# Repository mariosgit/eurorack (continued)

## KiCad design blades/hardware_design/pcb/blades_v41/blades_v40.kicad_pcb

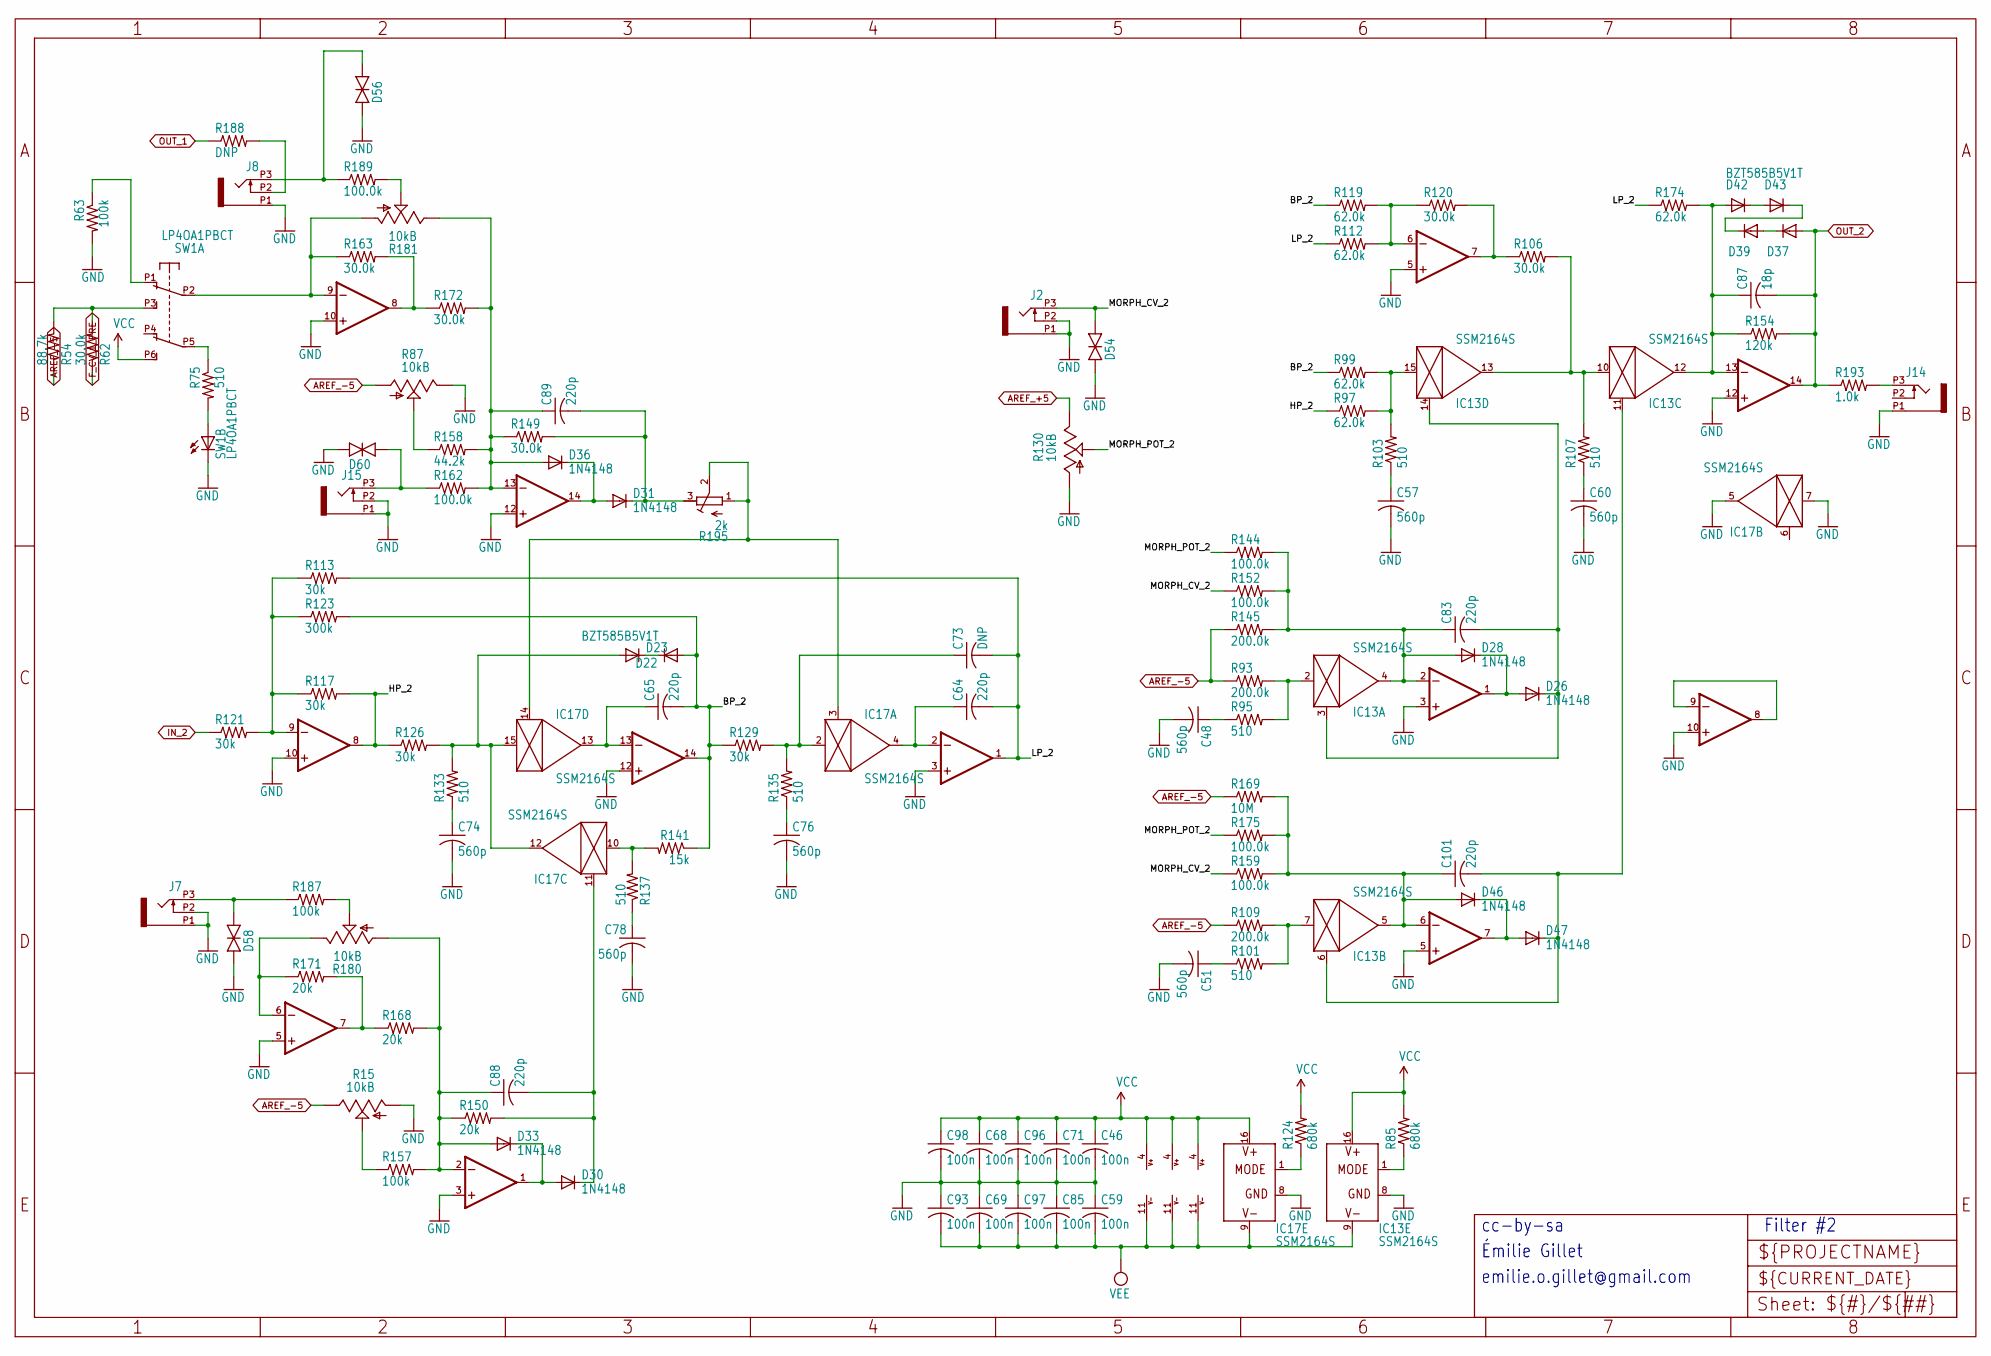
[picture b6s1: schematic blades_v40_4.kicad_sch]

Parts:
C46, C59, C68, C69, C71, C85, C93, C96, C97, C98: 100n; C0402
C48, C51, C57, C60, C74, C76, C78: 560p; C0402
C64, C65, C83, C88, C89, C101: 220p; C0402
C73: DNP; C0402
C87: 18p; C0402
D22, D23, D37, D39, D42, D43: BZT585B5V1T; SOD523
D26, D28, D30, D31, D33, D36, D46, D47: 1N4148; SOD523
D54, D56, D58, D60: TVS; 0603
IC13, IC17: SSM2164S; SOIC16N
IC15, IC21: OPA1679PW; TSSOP14_065
IC20: TL074PW; TSSOP14_065
J2, J7, J8, J14, J15: PJ301_THONKICONNTME; WQP_PJ_301M_TME
R15, R87, R130: 10kB; ALPS_POT_VERTICAL_PS
R54: 88.7k; R0402
R62, R106, R120, R149, R163, R172: 30.0k; R0402
R63, R157, R187: 100k; R0402
R75, R95, R101, R103, R107, R133, R135, R137: 510; R0402
R85, R124: 680k; R0402
R93, R109, R145: 200.0k; R0402
R97, R99, R112, R119, R174: 62.0k; R0402
R113, R117, R121, R126, R129: 30k; R0402
R123: 300k; R0402
R141: 15k; R0402
R144, R152, R159, R162, R175, R189: 100.0k; R0402
R150, R168, R171: 20k; R0402
R154: 120k; R0402
R158: 44.2k; R0402
R169: 10M; R0402
R180, R181: 10kB; ALPS_POT_NARROW
R188: DNP; R0603
R193: 1.0k; R0603
R195: 2k; RTRIM3296W
SW1: LP4OA1PBCT

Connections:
/blades_v40_4/BP_2: C65.2, D22.A, IC15.14 (OUT), R99.1, R119.1, R123.2, R129.1, R141.1
/blades_v40_4/HP_2: IC15.8 (OUT), R97.1, R117.2, R126.1
/blades_v40_4/LP_2: C64.2, C73.2, IC15.1 (OUT), R112.1, R113.2, R174.1
/blades_v40_4/MORPH_CV_2: D54.2 (C), J2.P3 (3), R152.1, R159.1
/blades_v40_4/MORPH_POT_2: R130.P$2 (S), R144.1, R175.1
AREF_+5: R130.P$1 (E); also elsewhere on the board
AREF_-5: R15.P$1 (E), R54.1, R87.P$3 (A), R93.1, R109.1, R145.1, R169.1; also elsewhere on the board
F_CV_1_PRE: R62.1; also elsewhere on the board
GND: C46.2, C48.2, C51.2, C57.2, C59.1, C60.2, C68.2, C69.1, C71.2, C74.2, C76.2, C78.2, C85.1, C93.1, C96.2, C97.1, C98.2, D54.1 (A), D56.1 (A), D58.1 (A), D60.1 (A), IC13.8 (GND), IC15.3 (+IN), IC15.5 (+IN), IC15.10 (+IN), IC15.12 (+IN), IC17.5 (OUT), IC17.7 (IN), IC17.8 (GND), IC20.3 (+IN), IC20.5 (+IN), IC20.10 (+IN), IC20.12 (+IN), IC21.3 (+IN), IC21.5 (+IN), IC21.10 (+IN), IC21.12 (+IN), J2.P1 (1), J2.P2 (2), J7.P1 (1), J7.P2 (2), J8.P1 (1), J14.P1 (1), J15.P1 (1), J15.P2 (2), R15.P$3 (A), R63.2, R87.P$1 (E), R130.P$3 (A), SW1.L2; also elsewhere on the board
IN_2: R121.1; also elsewhere on the board
unnamed: C48.1, R95.1
unnamed: C51.1, R101.1
unnamed: C57.1, R103.1
unnamed: C60.1, R107.1
unnamed: C74.1, R133.1
unnamed: C76.1, R135.1
unnamed: C78.1, R137.1
unnamed: D22.C, D23.C
unnamed: D37.C, D39.A
unnamed: D39.C, D43.C
unnamed: D42.C, D43.A
unnamed: D56.2 (C), J8.P3 (3), R189.1
unnamed: D58.2 (C), J7.P3 (3), R187.1
unnamed: D60.2 (C), J15.P3 (3), R162.1
unnamed: C83.2, D26.C, IC13.3 (CTRL), IC13.14 (CTRL)
unnamed: IC13.2 (IN), R93.2, R95.2
unnamed: C83.1, D28.A, IC13.4 (OUT), IC21.2 (-IN), R144.2, R145.2, R152.2
unnamed: C101.2, D47.C, IC13.6 (CTRL), IC13.11 (CTRL)
unnamed: IC13.7 (IN), R101.2, R109.2
unnamed: C101.1, D46.A, IC13.5 (OUT), IC21.6 (-IN), R159.2, R169.2, R175.2
unnamed: IC13.10 (IN), IC13.13 (OUT), R106.2, R107.2
unnamed: C87.1, D42.A, IC13.12 (OUT), IC21.13 (-IN), R154.1, R174.2
unnamed: IC13.15 (IN), R97.2, R99.2, R103.2
unnamed: IC13.1 (MODE), R85.1
unnamed: C64.1, IC15.2 (-IN), IC17.4 (OUT)
unnamed: IC15.6 (-IN), R112.2, R119.2, R120.1
unnamed: IC15.7 (OUT), R106.1, R120.2
unnamed: IC15.9 (-IN), R113.1, R117.1, R121.2, R123.1
unnamed: C65.1, IC15.13 (-IN), IC17.13 (OUT)
unnamed: IC17.3 (CTRL), IC17.14 (CTRL), R195.1 (E), R195.2 (S)
unnamed: C73.1, IC17.2 (IN), R129.2, R135.2
unnamed: C88.2, D30.C, IC17.11 (CTRL), R150.2
unnamed: IC17.10 (IN), R137.2, R141.2
unnamed: D23.A, IC17.12 (OUT), IC17.15 (IN), R126.2, R133.2
unnamed: IC17.1 (MODE), R124.1
unnamed: C88.1, D33.A, IC20.2 (-IN), R150.1, R157.2, R168.2, R180.P$3 (A)
unnamed: D30.A, D33.C, IC20.1 (OUT)
unnamed: IC20.6 (-IN), R171.1, R180.P$1 (E)
unnamed: IC20.7 (OUT), R168.1, R171.2
unnamed: IC20.9 (-IN), R163.1, R181.P$3 (A), SW1.P2 (A2)
unnamed: IC20.8 (OUT), R163.2, R172.1
unnamed: C89.1, D36.A, IC20.13 (-IN), R149.1, R158.2, R162.2, R172.2, R181.P$1 (E)
unnamed: D31.A, D36.C, IC20.14 (OUT)
unnamed: D26.A, D28.C, IC21.1 (OUT)
unnamed: D46.C, D47.A, IC21.7 (OUT)
unnamed: IC21.8 (OUT), IC21.9 (-IN)
unnamed: J8.P2 (2), R188.2
unnamed: J14.P3 (3), R193.2
unnamed: R15.P$2 (S), R157.1
unnamed: R75.2, SW1.L1
unnamed: R87.P$2 (S), R158.1
unnamed: R180.P$2 (S), R187.2
unnamed: R181.P$2 (S), R189.2
unnamed: C89.2, D31.C, R149.2, R195.3 (A)
unnamed: R63.1, SW1.P1 (A1)
unnamed: R54.2, R62.2, SW1.P3 (A3)
unnamed: R75.1, SW1.P5 (B2)
OUT_1: R188.1; also elsewhere on the board
OUT_2: C87.2, D37.A, IC21.14 (OUT), R154.2, R193.1; also elsewhere on the board
VCC: C46.1, C68.1, C71.1, C96.1, C98.1, IC13.16 (V+), IC15.4 (V+), IC17.16 (V+), IC20.4 (V+), IC21.4 (V+), R85.2, R124.2, SW1.P6 (B3); also elsewhere on the board
VEE: C59.2, C69.2, C85.2, C93.2, C97.2, IC13.9 (V-), IC15.11 (V-), IC17.9 (V-), IC20.11 (V-), IC21.11 (V-); also elsewhere on the board

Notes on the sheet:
cc-by-sa
Filter #2
emilie.o.gillet@gmail.com
Émilie Gillet

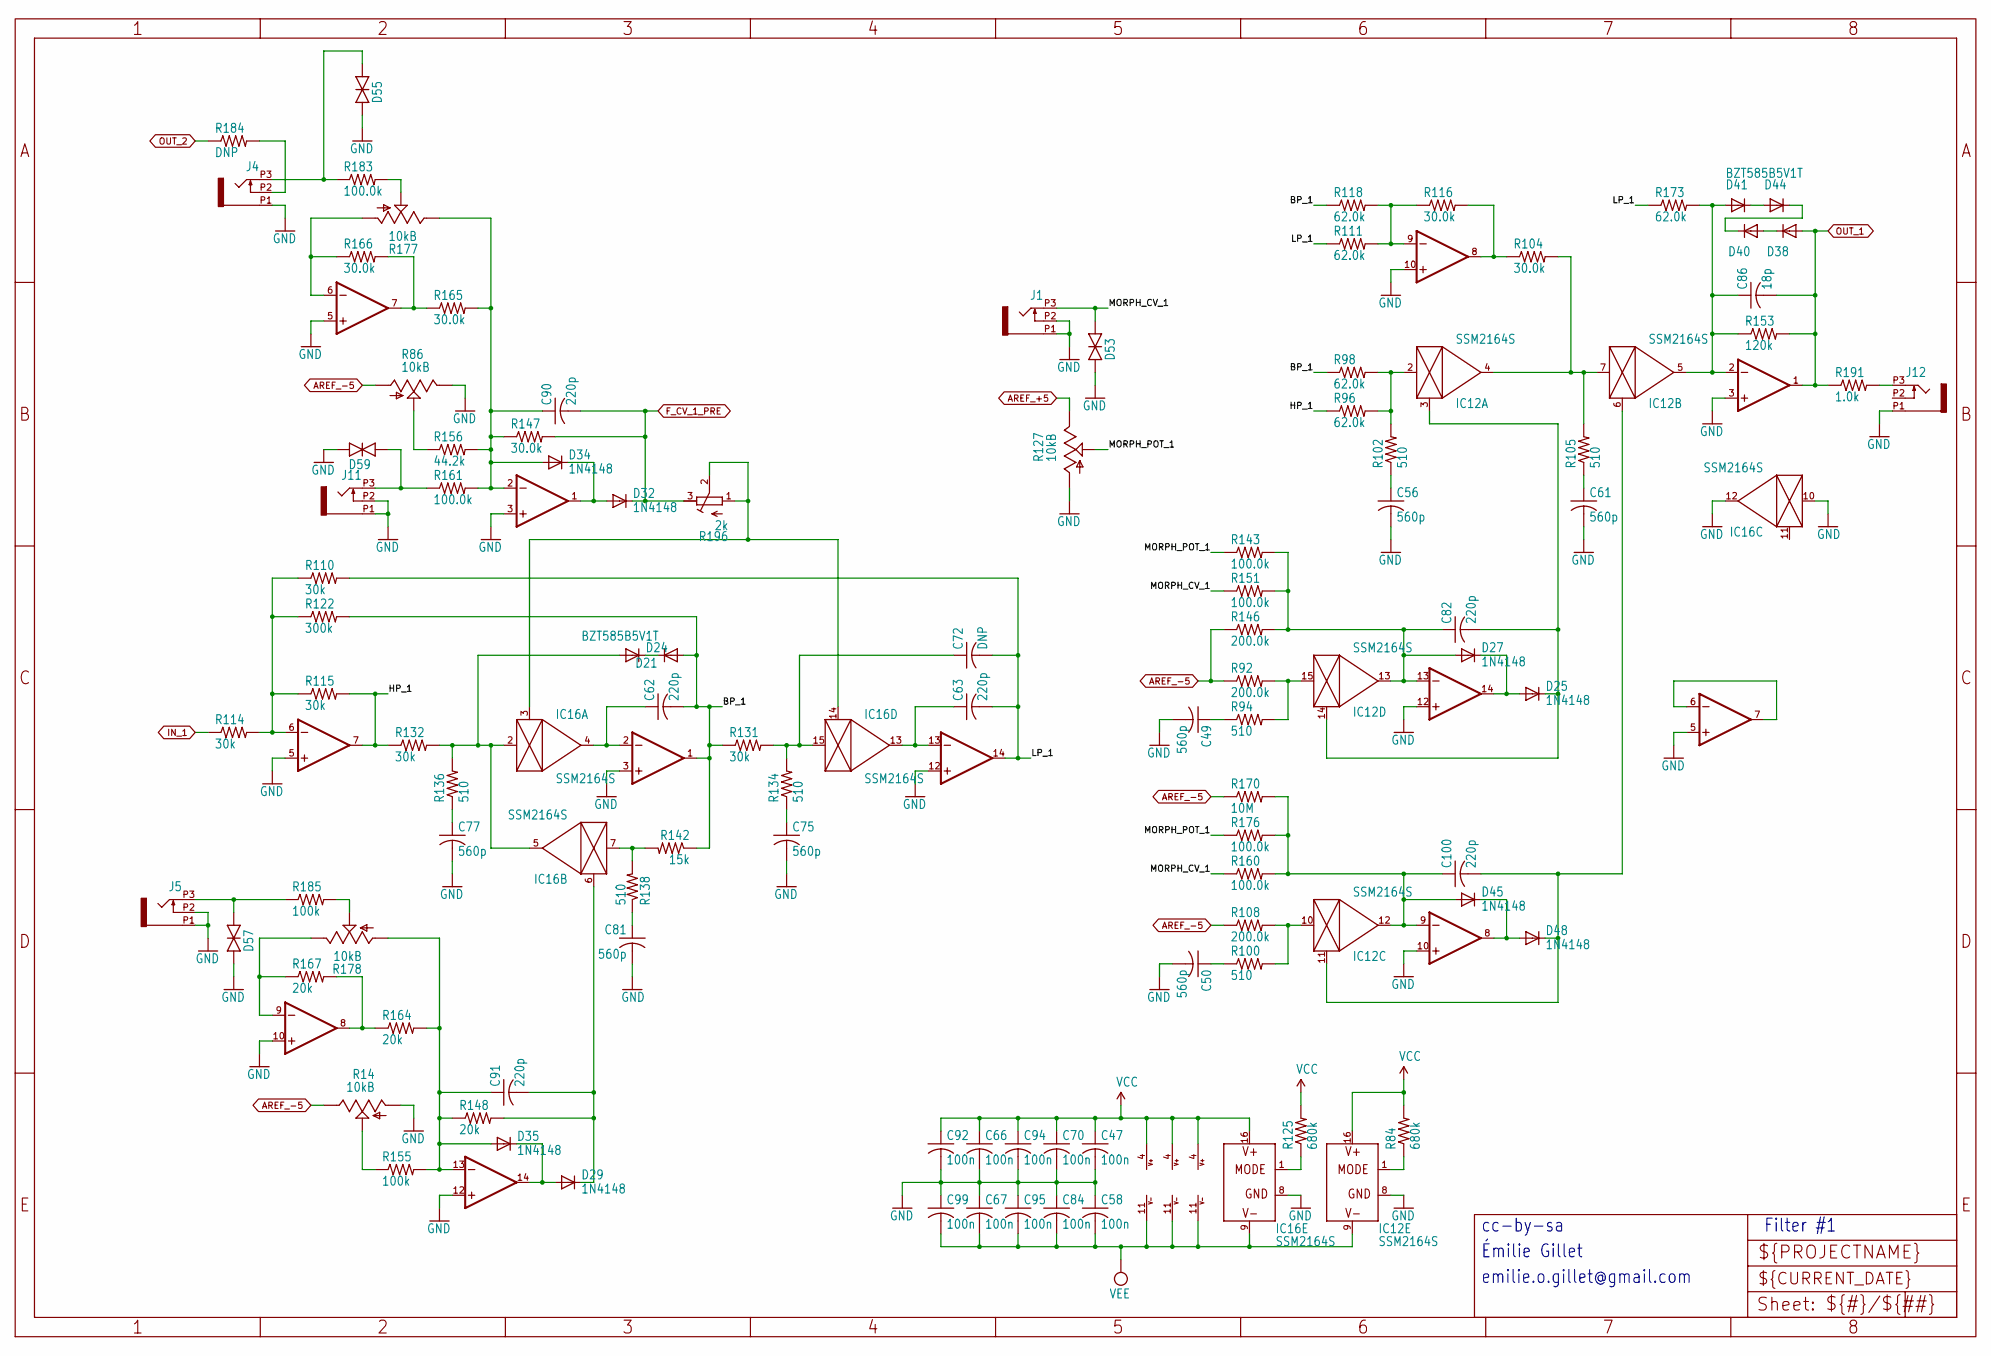
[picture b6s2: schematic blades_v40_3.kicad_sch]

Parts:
C47, C58, C66, C67, C70, C84, C92, C94, C95, C99: 100n; C0402
C49, C50, C56, C61, C75, C77, C81: 560p; C0402
C62, C63, C82, C90, C91, C100: 220p; C0402
C72: DNP; C0402
C86: 18p; C0402
D21, D24, D38, D40, D41, D44: BZT585B5V1T; SOD523
D25, D27, D29, D32, D34, D35, D45, D48: 1N4148; SOD523
D53, D55, D57, D59: TVS; 0603
IC12, IC16: SSM2164S; SOIC16N
IC14, IC18: OPA1679PW; TSSOP14_065
IC19: TL074PW; TSSOP14_065
J1, J4, J5, J11, J12: PJ301_THONKICONNTME; WQP_PJ_301M_TME
R14, R86, R127: 10kB; ALPS_POT_VERTICAL_PS
R84, R125: 680k; R0402
R92, R108, R146: 200.0k; R0402
R94, R100, R102, R105, R134, R136, R138: 510; R0402
R96, R98, R111, R118, R173: 62.0k; R0402
R104, R116, R147, R165, R166: 30.0k; R0402
R110, R114, R115, R131, R132: 30k; R0402
R122: 300k; R0402
R142: 15k; R0402
R143, R151, R160, R161, R176, R183: 100.0k; R0402
R148, R164, R167: 20k; R0402
R153: 120k; R0402
R155, R185: 100k; R0402
R156: 44.2k; R0402
R170: 10M; R0402
R177, R178: 10kB; ALPS_POT_NARROW
R184: DNP; R0603
R191: 1.0k; R0603
R196: 2k; RTRIM3296W

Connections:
/blades_v40_3/BP_1: C62.2, D21.A, IC14.1 (OUT), R98.1, R118.1, R122.2, R131.1, R142.1
/blades_v40_3/HP_1: IC14.7 (OUT), R96.1, R115.2, R132.1
/blades_v40_3/LP_1: C63.2, C72.2, IC14.14 (OUT), R110.2, R111.1, R173.1
/blades_v40_3/MORPH_CV_1: D53.2 (C), J1.P3 (3), R151.1, R160.1
/blades_v40_3/MORPH_POT_1: R127.P$2 (S), R143.1, R176.1
AREF_+5: R127.P$1 (E); also elsewhere on the board
AREF_-5: R14.P$1 (E), R86.P$3 (A), R92.1, R108.1, R146.1, R170.1; also elsewhere on the board
F_CV_1_PRE: C90.2, D32.C, R147.2, R196.3 (A); also elsewhere on the board
GND: C47.2, C49.2, C50.2, C56.2, C58.1, C61.2, C66.2, C67.1, C70.2, C75.2, C77.2, C81.2, C84.1, C92.2, C94.2, C95.1, C99.1, D53.1 (A), D55.1 (A), D57.1 (A), D59.1 (A), IC12.8 (GND), IC14.3 (+IN), IC14.5 (+IN), IC14.10 (+IN), IC14.12 (+IN), IC16.8 (GND), IC16.10 (IN), IC16.12 (OUT), IC18.3 (+IN), IC18.5 (+IN), IC18.10 (+IN), IC18.12 (+IN), IC19.3 (+IN), IC19.5 (+IN), IC19.10 (+IN), IC19.12 (+IN), J1.P1 (1), J1.P2 (2), J4.P1 (1), J5.P1 (1), J5.P2 (2), J11.P1 (1), J11.P2 (2), J12.P1 (1), R14.P$3 (A), R86.P$1 (E), R127.P$3 (A); also elsewhere on the board
IN_1: R114.1; also elsewhere on the board
unnamed: C49.1, R94.1
unnamed: C50.1, R100.1
unnamed: C56.1, R102.1
unnamed: C61.1, R105.1
unnamed: C75.1, R134.1
unnamed: C77.1, R136.1
unnamed: C81.1, R138.1
unnamed: D21.C, D24.C
unnamed: D38.C, D40.A
unnamed: D40.C, D44.C
unnamed: D41.C, D44.A
unnamed: D55.2 (C), J4.P3 (3), R183.1
unnamed: D57.2 (C), J5.P3 (3), R185.1
unnamed: D59.2 (C), J11.P3 (3), R161.1
unnamed: C82.2, D25.C, IC12.3 (CTRL), IC12.14 (CTRL)
unnamed: IC12.2 (IN), R96.2, R98.2, R102.2
unnamed: IC12.4 (OUT), IC12.7 (IN), R104.2, R105.2
unnamed: C100.2, D48.C, IC12.6 (CTRL), IC12.11 (CTRL)
unnamed: C86.1, D41.A, IC12.5 (OUT), IC18.2 (-IN), R153.1, R173.2
unnamed: IC12.10 (IN), R100.2, R108.2
unnamed: C100.1, D45.A, IC12.12 (OUT), IC18.9 (-IN), R160.2, R170.2, R176.2
unnamed: IC12.15 (IN), R92.2, R94.2
unnamed: C82.1, D27.A, IC12.13 (OUT), IC18.13 (-IN), R143.2, R146.2, R151.2
unnamed: IC12.1 (MODE), R84.1
unnamed: C62.1, IC14.2 (-IN), IC16.4 (OUT)
unnamed: IC14.6 (-IN), R110.1, R114.2, R115.1, R122.1
unnamed: IC14.9 (-IN), R111.2, R116.1, R118.2
unnamed: IC14.8 (OUT), R104.1, R116.2
unnamed: C63.1, IC14.13 (-IN), IC16.13 (OUT)
unnamed: IC16.3 (CTRL), IC16.14 (CTRL), R196.1 (E), R196.2 (S)
unnamed: D24.A, IC16.2 (IN), IC16.5 (OUT), R132.2, R136.2
unnamed: C91.2, D29.C, IC16.6 (CTRL), R148.2
unnamed: IC16.7 (IN), R138.2, R142.2
unnamed: C72.1, IC16.15 (IN), R131.2, R134.2
unnamed: IC16.1 (MODE), R125.1
unnamed: IC18.6 (-IN), IC18.7 (OUT)
unnamed: D45.C, D48.A, IC18.8 (OUT)
unnamed: D25.A, D27.C, IC18.14 (OUT)
unnamed: C90.1, D34.A, IC19.2 (-IN), R147.1, R156.2, R161.2, R165.2, R177.P$1 (E)
unnamed: D32.A, D34.C, IC19.1 (OUT)
unnamed: IC19.6 (-IN), R166.1, R177.P$3 (A)
unnamed: IC19.7 (OUT), R165.1, R166.2
unnamed: IC19.9 (-IN), R167.1, R178.P$1 (E)
unnamed: IC19.8 (OUT), R164.1, R167.2
unnamed: C91.1, D35.A, IC19.13 (-IN), R148.1, R155.2, R164.2, R178.P$3 (A)
unnamed: D29.A, D35.C, IC19.14 (OUT)
unnamed: J4.P2 (2), R184.2
unnamed: J12.P3 (3), R191.2
unnamed: R14.P$2 (S), R155.1
unnamed: R86.P$2 (S), R156.1
unnamed: R177.P$2 (S), R183.2
unnamed: R178.P$2 (S), R185.2
OUT_1: C86.2, D38.A, IC18.1 (OUT), R153.2, R191.1; also elsewhere on the board
OUT_2: R184.1; also elsewhere on the board
VCC: C47.1, C66.1, C70.1, C92.1, C94.1, IC12.16 (V+), IC14.4 (V+), IC16.16 (V+), IC18.4 (V+), IC19.4 (V+), R84.2, R125.2; also elsewhere on the board
VEE: C58.2, C67.2, C84.2, C95.2, C99.2, IC12.9 (V-), IC14.11 (V-), IC16.9 (V-), IC18.11 (V-), IC19.11 (V-); also elsewhere on the board

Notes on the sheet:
cc-by-sa
Émilie Gillet
Filter #1
emilie.o.gillet@gmail.com

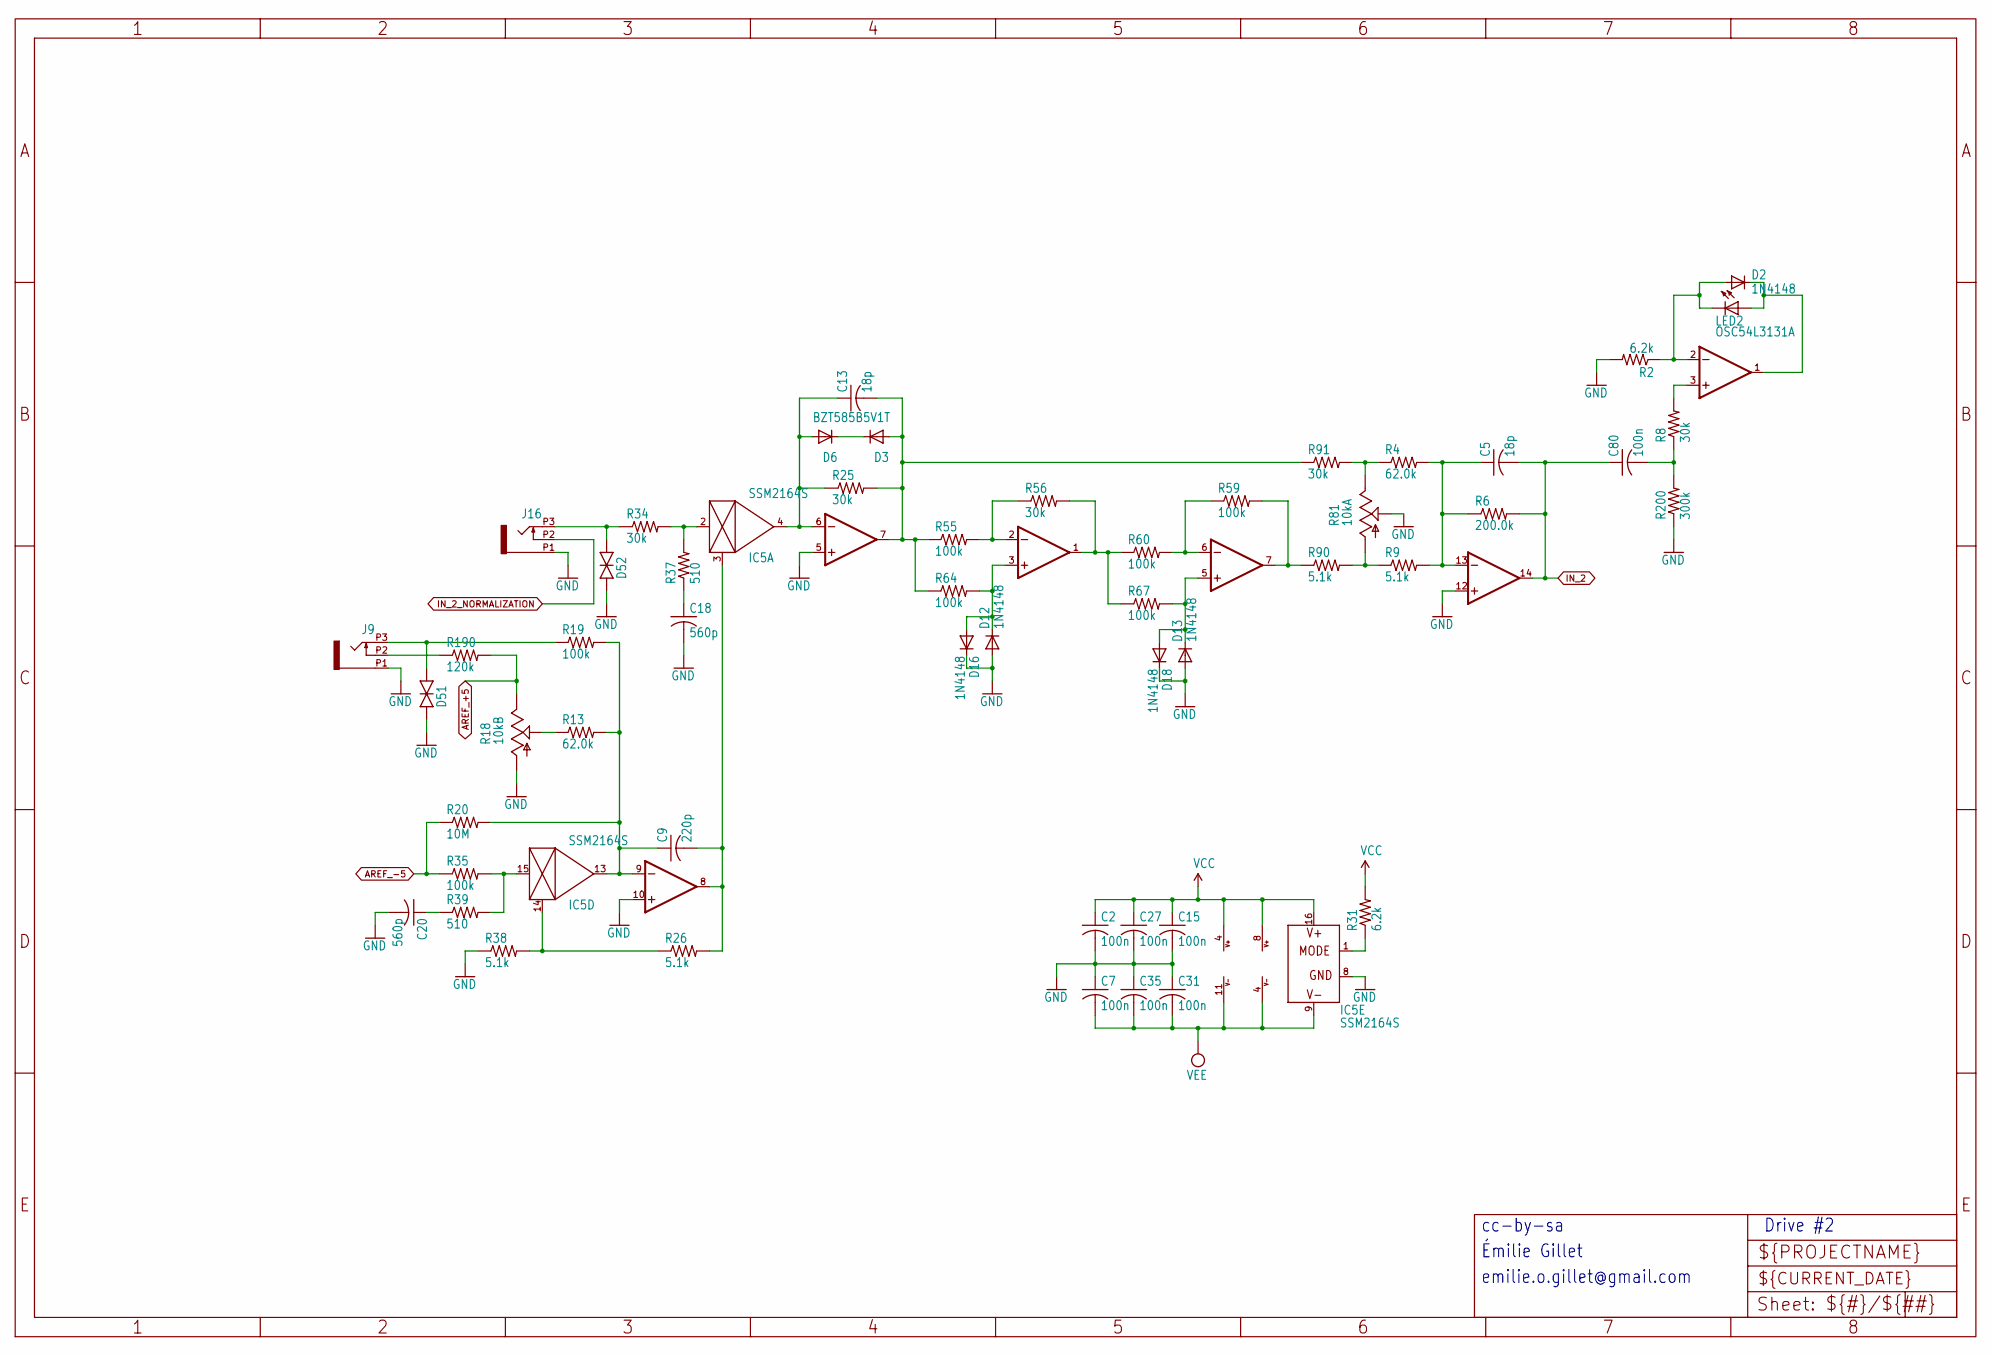
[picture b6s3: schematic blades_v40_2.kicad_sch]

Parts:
C2, C7, C15, C27, C31, C35, C80: 100n; C0402
C5, C13: 18p; C0402
C9: 220p; C0402
C18, C20: 560p; C0402
D2, D12, D13, D16, D18: 1N4148; SOD523
D3, D6: BZT585B5V1T; SOD523
D51, D52: TVS; 0603
IC1: OPA1679PW; TSSOP14_065
IC5: SSM2164S; SOIC16N
IC7: OPA1678DGK; VSSOP8
J9, J16: PJ301_THONKICONNTME; WQP_PJ_301M_TME
LED2: OSC54L3131A; LED3MM
R2, R31: 6.2k; R0402
R4, R13: 62.0k; R0402
R6: 200.0k; R0402
R8, R25, R34, R56, R91: 30k; R0402
R9, R26, R38, R90: 5.1k; R0402
R18: 10kB; ALPS_POT_VERTICAL_PS
R19, R35, R55, R59, R60, R64, R67: 100k; R0402
R20: 10M; R0402
R37, R39: 510; R0402
R81: 10kA; ALPS_POT_NARROW
R190: 120k; R0402
R200: 300k; R0402

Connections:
AREF_+5: R18.P$1 (E), R190.2; also elsewhere on the board
AREF_-5: R20.1, R35.1; also elsewhere on the board
GND: C2.2, C7.1, C15.2, C18.2, C20.2, C27.2, C31.1, C35.1, D12.A, D13.A, D16.C, D18.C, D51.1 (A), D52.1 (A), IC1.5 (+IN), IC1.10 (+IN), IC1.12 (+IN), IC5.8 (GND), J9.P1 (1), J16.P1 (1), R2.2, R18.P$3 (A), R38.1, R81.P$2 (S), R200.1; also elsewhere on the board
IN_2: C5.2, C80.1, IC1.14 (OUT), R6.2; also elsewhere on the board
IN_2_NORMALIZATION: J16.P2 (2); also elsewhere on the board
unnamed: C18.1, R37.1
unnamed: C20.1, R39.1
unnamed: C80.2, R8.1, R200.2
unnamed: D3.C, D6.C
unnamed: D51.2 (C), J9.P3 (3), R19.1
unnamed: D52.2 (C), J16.P3 (3), R34.1
unnamed: IC1.3 (+IN), R8.2
unnamed: D2.A, IC1.2 (-IN), LED2.K (C), R2.1
unnamed: D2.C, IC1.1 (OUT), LED2.A
unnamed: C13.1, D6.A, IC1.6 (-IN), IC5.4 (OUT), R25.1
unnamed: C13.2, D3.A, IC1.7 (OUT), R25.2, R55.1, R64.1, R91.1
unnamed: C9.1, IC1.9 (-IN), IC5.13 (OUT), R13.2, R19.2, R20.2
unnamed: C9.2, IC1.8 (OUT), IC5.3 (CTRL), R26.2
unnamed: C5.1, IC1.13 (-IN), R4.2, R6.1, R9.2
unnamed: IC5.2 (IN), R34.2, R37.2
unnamed: IC5.14 (CTRL), R26.1, R38.2
unnamed: IC5.15 (IN), R35.2, R39.2
unnamed: IC5.1 (MODE), R31.1
unnamed: D12.C, D16.A, IC7.3 (+IN), R64.2
unnamed: IC7.2 (-IN), R55.2, R56.1
unnamed: IC7.1 (OUT), R56.2, R60.1, R67.1
unnamed: D13.C, D18.A, IC7.5 (+IN), R67.2
unnamed: IC7.6 (-IN), R59.1, R60.2
unnamed: IC7.7 (OUT), R59.2, R90.1
unnamed: J9.P2 (2), R190.1
unnamed: R13.1, R18.P$2 (S)
unnamed: R9.1, R81.P$3 (A), R90.2
unnamed: R4.1, R81.P$1 (E), R91.2
VCC: C2.1, C15.1, C27.1, IC1.4 (V+), IC5.16 (V+), IC7.8 (V+), R31.2; also elsewhere on the board
VEE: C7.2, C31.2, C35.2, IC1.11 (V-), IC5.9 (V-), IC7.4 (V-); also elsewhere on the board

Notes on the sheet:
emilie.o.gillet@gmail.com
cc-by-sa
Drive #2
Émilie Gillet

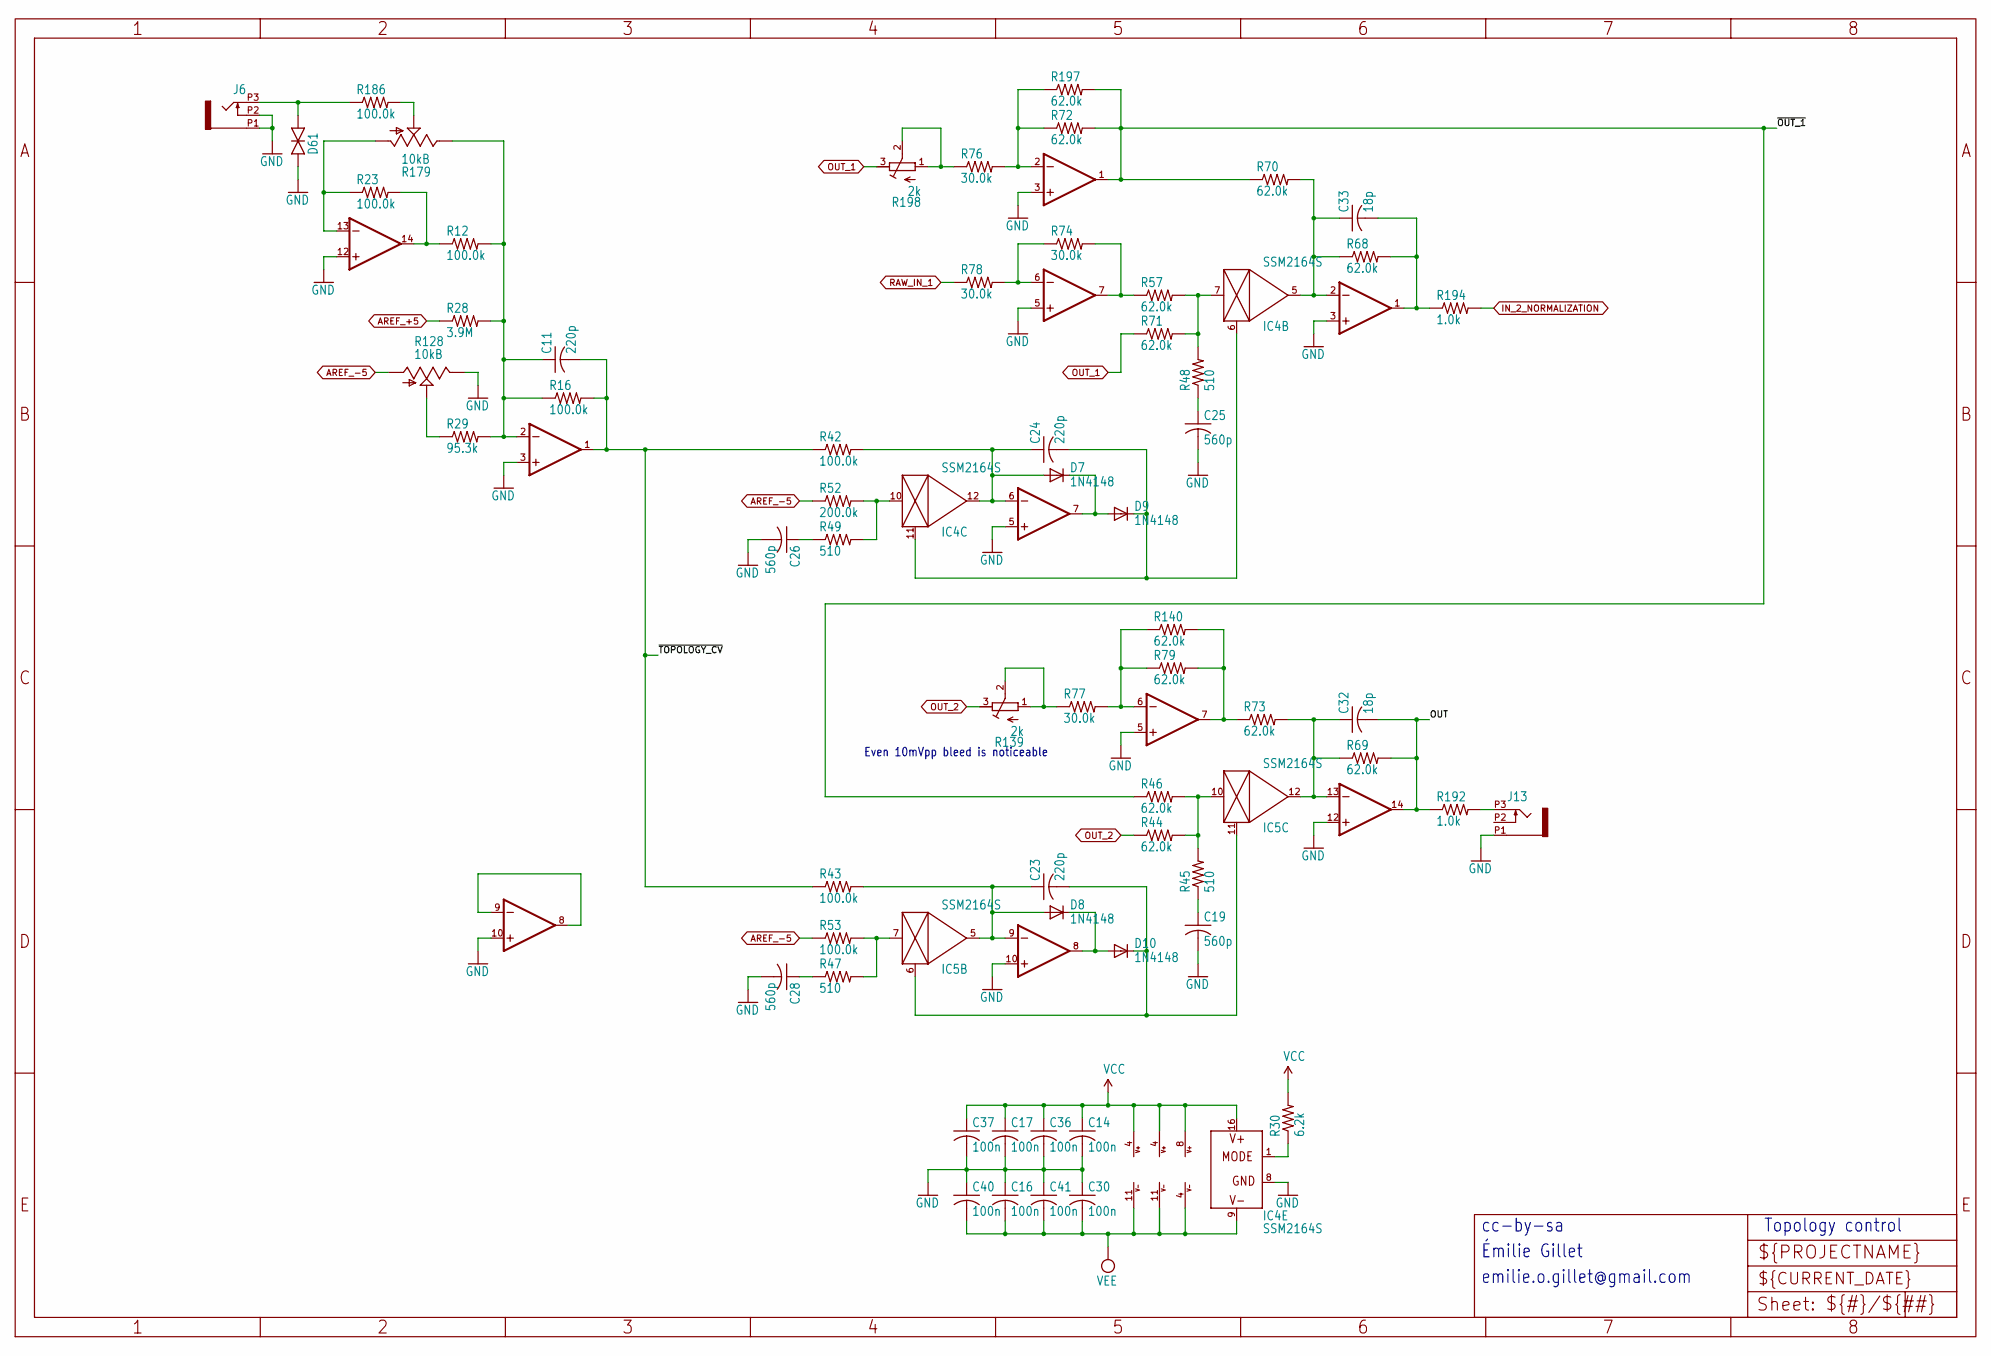
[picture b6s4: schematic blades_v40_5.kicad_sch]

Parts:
C11, C23, C24: 220p; C0402
C14, C16, C17, C30, C36, C37, C40, C41: 100n; C0402
C19, C25, C26, C28: 560p; C0402
C32, C33: 18p; C0402
D7, D8, D9, D10: 1N4148; SOD523
D61: TVS; 0603
IC3: TL074PW; TSSOP14_065
IC4, IC5: SSM2164S; SOIC16N
IC8: OPA1679PW; TSSOP14_065
IC9: OPA1678DGK; VSSOP8
J6, J13: PJ301_THONKICONNTME; WQP_PJ_301M_TME
R12, R16, R23, R42, R43, R53, R186: 100.0k; R0402
R28: 3.9M; R0402
R29: 95.3k; R0402
R30: 6.2k; R0402
R44, R46, R57, R68, R69, R70, R71, R72, R73, R79, R140, R197: 62.0k; R0402
R45, R47, R48, R49: 510; R0402
R52: 200.0k; R0402
R74, R76, R77, R78: 30.0k; R0402
R128: 10kB; ALPS_POT_VERTICAL_PS
R139, R198: 2k; RTRIM3296W
R179: 10kB; ALPS_POT_NARROW
R192, R194: 1.0k; R0603

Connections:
/blades_v40_5/OUT: C32.2, IC8.14 (OUT), R69.2, R192.1
/blades_v40_5/~OUT_1: IC9.1 (OUT), R46.1, R70.1, R72.2, R197.2
/blades_v40_5/~TOPOLOGY_CV: C11.2, IC3.1 (OUT), R16.2, R42.1, R43.1
AREF_+5: R28.1; also elsewhere on the board
AREF_-5: R52.1, R53.1, R128.P$3 (A); also elsewhere on the board
GND: C14.2, C16.1, C17.2, C19.2, C25.2, C26.2, C28.2, C30.1, C36.2, C37.2, C40.1, C41.1, D61.1 (A), IC3.3 (+IN), IC3.5 (+IN), IC3.10 (+IN), IC3.12 (+IN), IC4.8 (GND), IC8.3 (+IN), IC8.5 (+IN), IC8.10 (+IN), IC8.12 (+IN), IC9.3 (+IN), IC9.5 (+IN), J6.P1 (1), J6.P2 (2), J13.P1 (1), R128.P$1 (E); also elsewhere on the board
IN_2_NORMALIZATION: R194.2; also elsewhere on the board
unnamed: C19.1, R45.1
unnamed: C25.1, R48.1
unnamed: C26.1, R49.1
unnamed: C28.1, R47.1
unnamed: D61.2 (C), J6.P3 (3), R186.1
unnamed: C11.1, IC3.2 (-IN), R12.2, R16.1, R28.2, R29.2, R179.P$1 (E)
unnamed: C24.1, D7.A, IC3.6 (-IN), IC4.12 (OUT), R42.2
unnamed: D7.C, D9.A, IC3.7 (OUT)
unnamed: C23.1, D8.A, IC3.9 (-IN), IC5.5 (OUT), R43.2
unnamed: D8.C, D10.A, IC3.8 (OUT)
unnamed: IC3.13 (-IN), R23.1, R179.P$3 (A)
unnamed: IC3.14 (OUT), R12.1, R23.2
unnamed: C24.2, D9.C, IC4.6 (CTRL), IC4.11 (CTRL)
unnamed: IC4.7 (IN), R48.2, R57.2, R71.2
unnamed: C33.1, IC4.5 (OUT), IC8.2 (-IN), R68.1, R70.2
unnamed: IC4.10 (IN), R49.2, R52.2
unnamed: IC4.1 (MODE), R30.1
unnamed: C23.2, D10.C, IC5.6 (CTRL), IC5.11 (CTRL)
unnamed: IC5.7 (IN), R47.2, R53.2
unnamed: IC5.10 (IN), R44.2, R45.2, R46.2
unnamed: C32.1, IC5.12 (OUT), IC8.13 (-IN), R69.1, R73.2
unnamed: C33.2, IC8.1 (OUT), R68.2, R194.1
unnamed: IC8.6 (-IN), R77.2, R79.1, R140.1
unnamed: IC8.7 (OUT), R73.1, R79.2, R140.2
unnamed: IC8.8 (OUT), IC8.9 (-IN)
unnamed: IC9.2 (-IN), R72.1, R76.2, R197.1
unnamed: IC9.6 (-IN), R74.1, R78.2
unnamed: IC9.7 (OUT), R57.1, R74.2
unnamed: J13.P3 (3), R192.2
unnamed: R29.1, R128.P$2 (S)
unnamed: R77.1, R139.1 (E), R139.2 (S)
unnamed: R179.P$2 (S), R186.2
unnamed: R76.1, R198.1 (E), R198.2 (S)
OUT_1: R71.1, R198.3 (A); also elsewhere on the board
OUT_2: R44.1, R139.3 (A); also elsewhere on the board
RAW_IN_1: R78.1; also elsewhere on the board
VCC: C14.1, C17.1, C36.1, C37.1, IC3.4 (V+), IC4.16 (V+), IC8.4 (V+), IC9.8 (V+), R30.2; also elsewhere on the board
VEE: C16.2, C30.2, C40.2, C41.2, IC3.11 (V-), IC4.9 (V-), IC8.11 (V-), IC9.4 (V-); also elsewhere on the board

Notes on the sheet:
Topology control
emilie.o.gillet@gmail.com
cc-by-sa
Even 10mVpp bleed is noticeable~{}
Émilie Gillet
